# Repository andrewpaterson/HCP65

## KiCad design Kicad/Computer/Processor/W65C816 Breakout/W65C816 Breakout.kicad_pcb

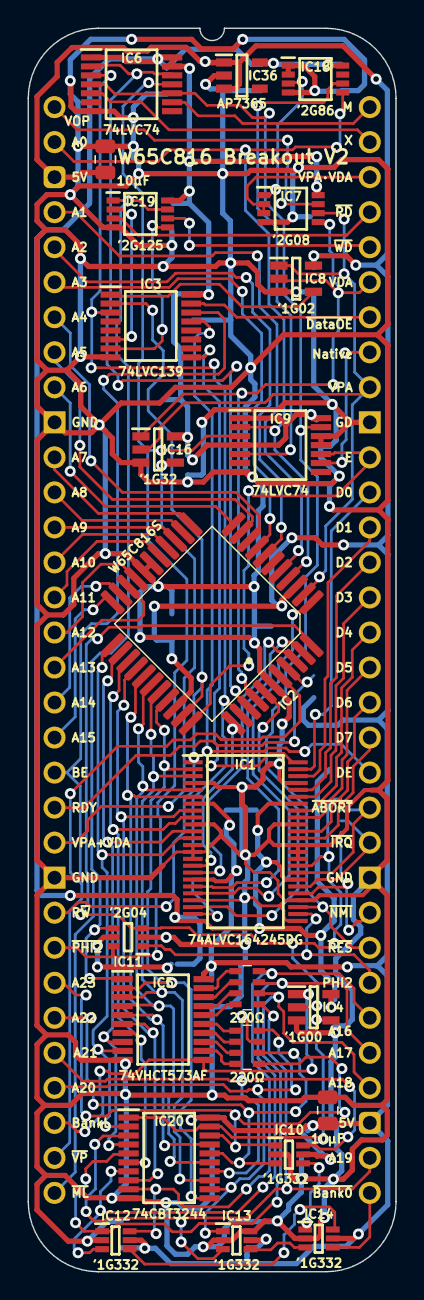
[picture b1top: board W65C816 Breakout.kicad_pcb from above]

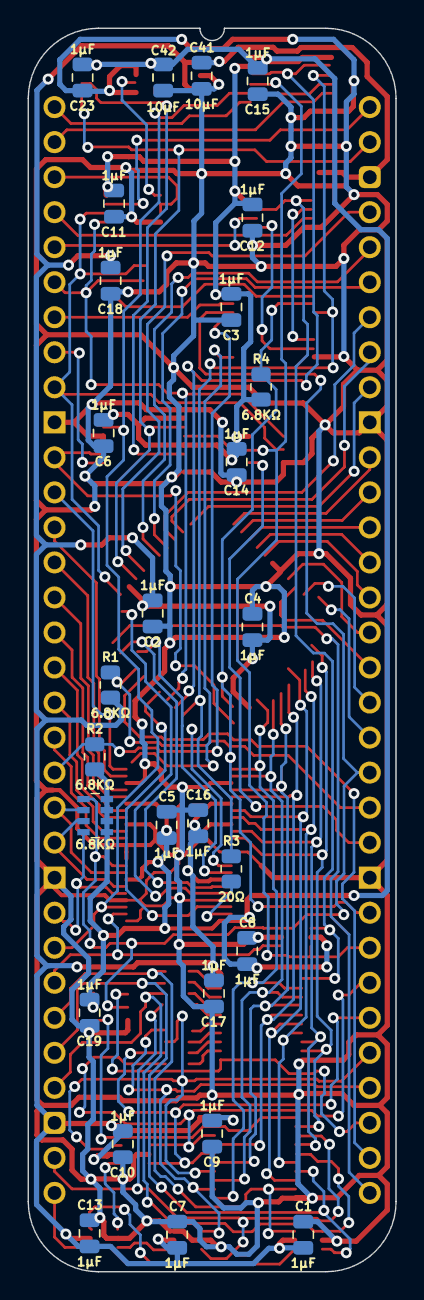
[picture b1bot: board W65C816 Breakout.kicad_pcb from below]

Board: 2 copper layers, 26.7 x 90.2 mm, 51 parts (27 on the bottom side), 96 nets.

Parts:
C1, C2, C3, C4, C5, C6, C7, C8, C9, C10, C11, C12, C13, C14, C15, C16, C17, C18, C19, C23: 1μF; C_0805
C20, C21, C41, C42: 10μF; C_0805
IC1: 74ALVC164245DGG,11; SOP50P810X120-48N
IC2: W65C816S6TQG-14; W65C816 PLCC 0.8mm 44 Pin
IC3: 74LVC139PW,118; SOP65P640X110-16N
IC4: 74LVC1G00GV,125; SOT95P275X110-5N
IC5: 74VHCT573AFT; SOP65P640X120-20N
IC6, IC9: 74LVC74APW,118; SOP65P640X110-14N
IC7: 74LVC2G08DP-Q100H; SOP65P400X110-8N
IC8: 74LVC1G02GV,125; SOT95P275X110-5N
IC10, IC12, IC13, IC14: SN74LVC1G332DCKRG4; SOT65P210X110-6N
IC11: 74LVC2G04GW-Q100H; SOP65P210X110-6N
IC16: 74LVC1G32GV,125; SOT95P275X110-5N
IC18: 74LVC2G86DP,125; SOP65P400X110-8N
IC19: 74LVC2G125DP,125; SOP65P400X110-8N
IC20: SN74CBT3244CPWR; SOP65P640X120-20N
IC36: AP7365-33WG-7; SOT95P285X130-5N
J7: Board 2x32 W22.86mm; DIP-64_Board_W22.86mm
R1, R2, R4: 6.8KΩ; R_0805
R3: 20Ω; R_0805
RN1, RN2: CAY16-221J4LF; CAY16-F4
RN4: CAY16-472J4LF; CAY16-F4

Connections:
5V: C1.1, C2.1, C4.1, C7.1, C9.1, C10.1, C13.1, C16.1, C17.1, C18.1, C20.1, C21.1, C41.1, IC1.7 (5V), IC1.18 (5V), IC2.9 (VCC), IC2.37 (VCC), IC5.20 (5V), IC8.5 (3V), IC10.5 (3V), IC12.5 (3V), IC13.5 (3V), IC14.5 (3V), IC20.20 (5V), IC36.1 (6VIn), IC36.3 (EN), J7.3, J7.35, R1.1
/3.3V: C3.1, C5.1, C6.1, C8.1, C11.1, C12.1, C14.1, C15.1, C19.1, C23.1, C42.1, IC1.24 (2DIR), IC1.31 (3V), IC1.42 (3V), IC3.16 (3V), IC4.5 (3V), IC6.1 (~1RD), IC6.13 (~2RD), IC6.14 (3V), IC7.8 (3V), IC9.1 (~1RD), IC9.4 (~1SD), IC9.14 (3V), IC11.5 (3V), IC16.5 (3V), IC18.8 (VCC), IC19.8 (VCC), IC36.5 (3.3VOut), R2.1, R4.1, RN4.1 (R1), RN4.2 (R2), RN4.3 (R3), RN4.4 (R4)
/A0_{CHANGE}: IC7.1 (1A), IC18.3 (2Y)
/A0_{PREV}: IC9.5 (1Q), IC18.6 (2B)
/BA0+BA1+BA2: IC12.4 (Y), IC14.6 (C)
/BA3+BA4: IC13.4 (Y), IC14.3 (B)
/BA5+BA6+BA7: IC10.4 (Y), IC14.1 (A)
/BE_{5V}: IC1.16 (2B2), IC2.40 (BE)
/D0_{65}: IC1.2 (1B0), IC2.36 (D0), IC5.2 (D0), IC20.11 (2A1)
/D0_{VHC}: IC5.19 (Q0), RN2.1 (R1)
/D1_{65}: IC1.3 (1B1), IC2.35 (D1), IC5.3 (D1), IC20.13 (2A2)
/D1_{VHC}: IC5.18 (Q1), RN2.2 (R2)
/D2_{65}: IC1.5 (1B2), IC2.34 (D2), IC5.4 (D2), IC20.15 (2A3)
/D2_{VHC}: IC5.17 (Q2), RN2.3 (R3)
/D3_{65}: IC1.6 (1B3), IC2.33 (D3), IC5.5 (D3), IC20.17 (2A4)
/D3_{VHC}: IC5.16 (Q3), RN2.4 (R4)
/D4_{65}: IC1.8 (1B4), IC2.32 (D4), IC5.6 (D4), IC20.8 (1A4)
/D4_{VHC}: IC5.15 (Q4), RN1.1 (R1)
/D5_{65}: IC1.9 (1B5), IC2.31 (D5), IC5.7 (D5), IC20.6 (1A3)
/D5_{VHC}: IC5.14 (Q5), RN1.2 (R2)
/D6_{65}: IC1.11 (1B6), IC2.30 (D6), IC5.8 (D6), IC20.4 (1A2)
/D6_{VHC}: IC5.13 (Q6), RN1.3 (R3)
/D7_{65}: IC1.12 (1B7), IC2.29 (D7), IC5.9 (D7), IC20.2 (1A1)
/D7_{VHC}: IC5.12 (Q7), RN1.4 (R4)
/FET ~OE: IC4.4 (Y), IC20.1 (1~OE), IC20.19 (2~OE)
/MX: IC2.42 (MX), IC6.2 (1D), IC6.12 (2D)
/PHI2_{5V}: IC2.41 (PHI2), IC3.3 (1A1), IC6.3 (1CP), R3.2
/~ABORT_{5V}: IC1.17 (2B3), IC2.4 (~ABORT)
/~BE: IC5.1 (~OE), IC11.4 (2Y), IC19.1 (1~OE), IC19.7 (2~OE)
/~DE: IC1.48 (1~OE), IC3.9 (~2Y3)
/~IRQ_{5V}: IC1.19 (2B4), IC2.5 (~IRQ)
/~NMI_{5V}: IC1.20 (2B5), IC2.7 (~NMI)
/~RD_{PART}: IC3.7 (~1Y3), IC19.5 (2A)
/~RES_{5V}: IC1.22 (2B6), IC2.44 (~RES)
/~VPA+VDA: IC3.1 (~1E), IC8.4 (Y)
/~WD_{PART}: IC3.6 (~1Y2), IC19.2 (1A)
A0: IC2.10 (A0), IC9.2 (1D), IC18.5 (2A), J7.2
A1: IC2.11 (A1), J7.4
A2: IC2.13 (A2), J7.5
A3: IC2.14 (A3), J7.6
A4: IC2.15 (A4), J7.7
A5: IC2.16 (A5), J7.8
A6: IC2.17 (A6), J7.9
A7: IC2.18 (A7), J7.11
A8: IC2.19 (A8), J7.12
A9: IC2.20 (A9), J7.13
A10: IC2.21 (A10), J7.14
A11: IC2.22 (A11), J7.15
A12: IC2.25 (A12), J7.16
A13: IC2.26 (A13), J7.17
A14: IC2.27 (A14), J7.18
A15: IC2.28 (A15), J7.19
Address Valid: IC16.4 (Y), J7.22
BA0: IC12.6 (C), IC20.9 (2B1), J7.38, RN2.8 (R1)
BA1: IC12.3 (B), IC20.7 (2B2), J7.37, RN2.7 (R2)
BA2: IC12.1 (A), IC20.5 (2B3), J7.36, RN2.6 (R3)
BA3: IC13.3 (B), IC20.3 (2B4), J7.34, RN2.5 (R4)
BA4: IC13.1 (A), IC20.12 (1B4), J7.29, RN1.8 (R1)
BA5: IC10.6 (C), IC20.14 (1B3), J7.28, RN1.7 (R2)
BA6: IC10.3 (B), IC20.16 (1B2), J7.27, RN1.6 (R3)
BA7: IC10.1 (A), IC20.18 (1B1), J7.26, RN1.5 (R4)
BE: IC1.33 (2A2), IC3.14 (2A0), IC4.2 (A), IC11.3 (2A), J7.20, RN4.5 (R4)
Bank Latch: IC4.1 (B), IC5.11 (LE), J7.30
D0: IC1.47 (1A0), J7.53
D1: IC1.46 (1A1), J7.52
D2: IC1.44 (1A2), J7.51
D3: IC1.43 (1A3), J7.50
D4: IC1.41 (1A4), J7.49
D5: IC1.40 (1A5), J7.48
D6: IC1.38 (1A6), J7.47
D7: IC1.37 (1A7), J7.46
DE: IC3.13 (2A1), J7.45, R2.2
E: IC2.39 (E), IC9.10 (~2SD), J7.54
GND: C1.2, C2.2, C3.2, C4.2, C5.2, C6.2, C7.2, C8.2, C9.2, C10.2, C11.2, C12.2, C13.2, C14.2, C15.2, C16.2, C17.2, C18.2, C19.2, C20.2, C21.2, C23.2, C41.2, C42.2, IC1.4 (GND), IC1.10 (GND), IC1.13 (2B0), IC1.14 (2B1), IC1.15 (GND), IC1.21 (GND), IC1.25 (2~OE), IC1.28 (GND), IC1.34 (GND), IC1.35 (2A1), IC1.36 (2A0), IC1.39 (GND), IC1.45 (GND), IC2.1 (GND), IC2.23 (GND), IC2.24 (GND), IC3.8 (GND), IC4.3 (GND), IC5.10 (GND), IC6.7 (GND), IC7.4 (GND), IC8.3 (GND), IC9.7 (GND), IC9.11 (2CP), IC9.12 (2D), IC10.2 (GND), IC11.2 (GND), IC12.2 (GND), IC13.2 (GND), IC13.6 (C), IC14.2 (GND), IC16.3 (GND), IC18.1 (1A), IC18.2 (1B), IC18.4 (GND), IC19.4 (GND), IC20.10 (GND), IC36.2 (GND), J7.10, J7.23, J7.42, J7.55
M: IC6.9 (2Q), J7.64
Native Latch: IC9.9 (2Q), J7.57
unnamed: IC1.23 (2B7), R3.1
Opcode Valid: IC7.7 (1Y), J7.1
PHI2: IC1.26 (2A7), IC11.1 (1A), J7.39
RDY: IC2.3 (RDY), J7.21, R1.2
R~W: IC1.1 (1DIR), IC2.38 (R~W), IC3.2 (1A0), J7.24, R4.2
VDA: IC2.43 (VDA), IC7.5 (2A), IC8.2 (A), IC16.1 (B), J7.59
VPA: IC2.8 (VPA), IC7.6 (2B), IC8.1 (B), IC16.2 (A), J7.56
VPA·VDA: IC7.2 (1B), IC7.3 (2Y), J7.62
X: IC6.5 (1Q), J7.63
~ABORT: IC1.32 (2A3), J7.44, RN4.6 (R3)
~BANK 0: IC14.4 (Y), J7.33
~Data Output: IC3.15 (~2E), J7.58
~IRQ: IC1.30 (2A4), J7.43, RN4.7 (R2)
~ML: IC2.6 (~ML), J7.32
~NMI: IC1.29 (2A5), J7.41, RN4.8 (R1)
~PHI2: IC6.11 (2CP), IC9.3 (1CP), IC11.6 (1Y), J7.25
~RD: IC19.3 (2Y), J7.61
~Reset: IC1.27 (2A6), IC6.4 (~1SD), IC6.10 (~2SD), IC9.13 (~2RD), J7.40
~VP: IC2.2 (~VP), J7.31
~WD: IC19.6 (1Y), J7.60

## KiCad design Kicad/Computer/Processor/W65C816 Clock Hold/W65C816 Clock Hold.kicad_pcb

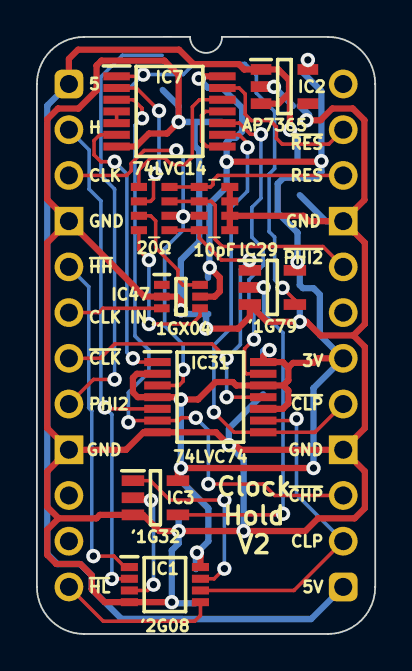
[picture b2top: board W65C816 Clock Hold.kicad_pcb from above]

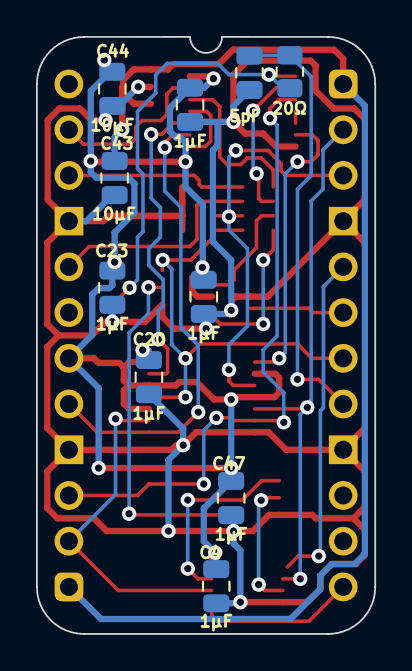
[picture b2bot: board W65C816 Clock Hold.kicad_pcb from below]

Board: 2 copper layers, 18.8 x 33.2 mm, 20 parts (10 on the bottom side), 28 nets.

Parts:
C1: 5pF; C_0805
C4, C20, C21, C23, C47, C56: 1μF; C_0805
C43, C44: 10μF; C_0805
CN1: CA0612KRX7R9BB100
IC1: 74LVC2G08DP-Q100H; SOP65P400X110-8N
IC2: AP7365-33WG-7; SOT95P285X130-5N
IC3: 74LVC1G32GV,125; SOT95P275X110-5N
IC7: SN74LVC14APWRG4; SOP65P640X110-14N
IC29: 74LVC1G79GV,125; SOT95P275X110-5N
IC31: 74LVC74APW,118; SOP65P640X110-14N
IC47: 74LVC1GX04GW,125; SOP65P210X110-6N
J1: Board 2x12 W22.86mm; DIP-24_Board_W15.24mm
R1: 20Ω; R_0805
RN1: CAY16-200J4LF; CAY16-F4

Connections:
3.3V: C4.1, C20.1, C21.1, C23.1, C44.1, C47.1, C56.1, IC1.8 (3V), IC2.5 (3.3VOut), IC3.5 (3V), IC7.14 (3V), IC29.5 (3V), IC31.2 (1D), IC31.4 (~1SD), IC31.10 (~2SD), IC31.12 (2D), IC31.14 (3V), IC47.5 (3V), J1.18
5V: C43.1, IC2.1 (6VIn), IC2.3 (EN), J1.1, J1.13
/CLK H.P.: IC7.4 (2Y), IC7.5 (3A)
/CLK L.P.: IC7.8 (4Y), IC7.11 (5A)
/High Pulse+Low Pulse: IC3.4 (Y), IC29.2 (CP)
/PHI2 Sharp: IC7.1 (1A), IC29.4 (Q), R1.2
/~CLK High Reset Pulse: IC7.6 (3Y), IC31.1 (~1RD)
/~CLK Low Reset Pulse: IC7.10 (5Y), IC31.13 (~2RD)
/~Hold High·CLK High Pulse·L=C: IC1.7 (1Y), IC3.1 (B)
/~Hold Low·CLK Low Pulse: IC1.3 (2Y), IC3.2 (A)
CLK: CN1.3, IC31.3 (1CP), J1.3, RN1.6 (R3)
CLK High Pulse: IC1.2 (1B), IC31.5 (1Q), J1.2
CLK IN: IC47.3 (X1), J1.6
CLK Low Pulse: IC1.6 (2B), IC31.9 (2Q), J1.14
GND: C1.2, C4.2, C20.2, C21.2, C23.2, C43.2, C44.2, C47.2, C56.2, CN1.5, CN1.6, CN1.7, CN1.8, IC1.4 (GND), IC2.2 (GND), IC3.3 (GND), IC7.7 (GND), IC29.3 (GND), IC31.7 (GND), IC47.2 (GND), J1.4, J1.9, J1.16, J1.21
unnamed: IC7.2 (1Y), RN1.2 (R2)
unnamed: IC7.12 (6Y), RN1.1 (R1)
unnamed: IC47.6 (Y), RN1.3 (R3)
unnamed: IC47.4 (~Y), RN1.4 (R4)
PHI2: C1.1, J1.8, R1.1
Reset: CN1.1, J1.22, RN1.8 (R1)
~CLK High Pulse: IC7.3 (2A), IC31.6 (~1Q), J1.15
~CLK Low Pulse: IC7.9 (4A), IC31.8 (~2Q), J1.17
~CLK: CN1.4, IC29.1 (D), IC31.11 (2CP), J1.7, RN1.5 (R4)
~Hold High: IC1.1 (1A), J1.5
~Hold Low: IC1.5 (2A), J1.12
~PHI2: CN1.2, J1.20, RN1.7 (R2)
~Reset: IC7.13 (6A), J1.23

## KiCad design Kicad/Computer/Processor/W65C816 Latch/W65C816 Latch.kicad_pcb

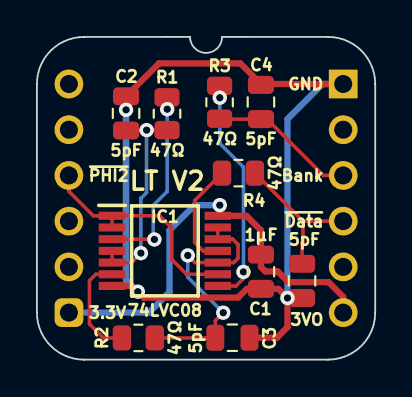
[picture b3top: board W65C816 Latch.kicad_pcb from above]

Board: 2 copper layers, 18.8 x 17.9 mm, 11 parts (0 on the bottom side), 11 nets.

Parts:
C1: 1μF; C_0805
C2, C3, C4, C5: 5pF; C_0805
IC1: 74LVC08APW,112; SOP65P640X110-14N
J2: Board 2x06 W15.24mm; DIP-12_Board_W15.24mm_Alt
R1, R2, R3, R4: 47Ω; R_0805

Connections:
3.3V: C1.1, IC1.14 (3V), J2.6, J2.7
/~PHI2_{2}: C2.1, IC1.4 (2A), IC1.5 (2B), R1.1
/~PHI2_{3}: C3.1, IC1.10 (3B), IC1.12 (4A), IC1.13 (4B), R2.1
Bank Latch: C4.1, J2.10, R3.1
GND: C1.2, C2.2, C3.2, C4.2, C5.2, IC1.7 (GND), J2.12
unnamed: IC1.3 (1Y), R1.2
unnamed: IC1.6 (2Y), R2.2
unnamed: IC1.8 (3Y), R3.2
unnamed: IC1.11 (4Y), R4.2
~Data Output: C5.1, J2.9, R4.1
~PHI2: IC1.1 (1A), IC1.2 (1B), IC1.9 (3A), J2.3

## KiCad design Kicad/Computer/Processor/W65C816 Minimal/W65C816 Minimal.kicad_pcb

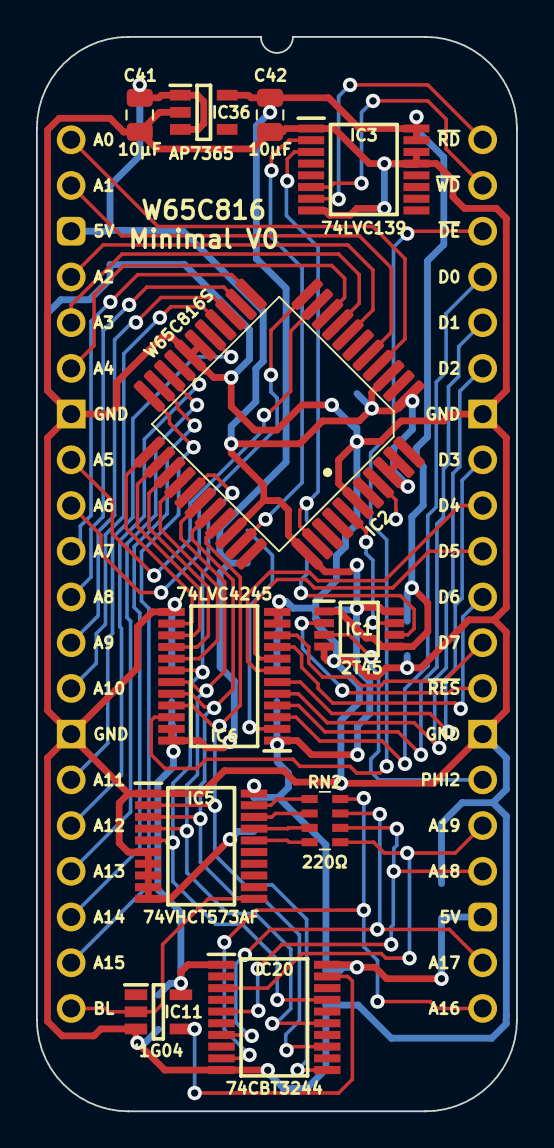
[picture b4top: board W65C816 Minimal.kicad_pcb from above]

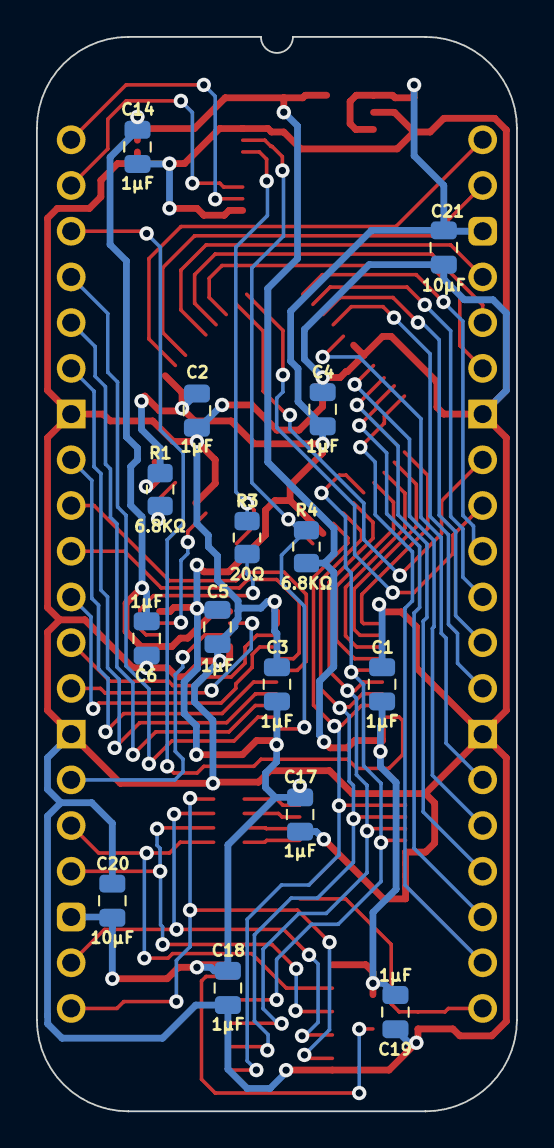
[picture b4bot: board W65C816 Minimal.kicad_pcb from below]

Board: 2 copper layers, 26.7 x 59.7 mm, 27 parts (15 on the bottom side), 55 nets.

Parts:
C1, C2, C3, C4, C5, C6, C14, C17, C18, C19: 1μF; C_0805
C20, C21, C41, C42: 10μF; C_0805
IC1: SN74LVC2T45DCTR; SOP65P400X130-8N
IC2: W65C816S6TQG-14; W65C816 PLCC 0.8mm 44 Pin
IC3: 74LVC139PW,118; SOP65P640X110-16N
IC5: 74VHCT573AFT; SOP65P640X120-20N
IC6: 74LVC4245APW,118; SOP65P640X110-24N
IC11: 74LVC1G04GV,125; SOT95P275X110-5N
IC20: SN74CBT3244CPWR; SOP65P640X120-20N
IC36: AP7365-33WG-7; SOT95P285X130-5N
J3: Board 2x20 W22.86mm; DIP-40_Board_W22.86mm
R1, R4: 6.8KΩ; R_0805
R3: 20Ω; R_0805
RN2: CAY16-221J4LF; CAY16-F4

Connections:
5V: C2.1, C3.1, C4.1, C5.1, C17.1, C18.1, C20.1, C21.1, C41.1, IC1.8 (5V), IC2.4 (~ABORT), IC2.5 (~IRQ), IC2.7 (~NMI), IC2.9 (VCC), IC2.37 (VCC), IC2.40 (BE), IC5.20 (5V), IC6.1 (5V), IC20.20 (5V), IC36.1 (6VIn), IC36.3 (EN), J3.3, J3.23, R1.2
/3.3V: C1.1, C6.1, C14.1, C19.1, C42.1, IC1.1 (3V), IC1.5 (DIR), IC3.15 (~2E), IC3.16 (3V), IC6.23 (3V), IC6.24 (3V), IC11.5 (3V), IC20.1 (1~OE), IC36.5 (3.3VOut), R4.1
/D0_{65}: IC2.36 (D0), IC5.2 (D0), IC6.21 (B0), IC20.11 (2A1)
/D0_{VHC}: IC5.19 (Q0), RN2.1 (R1)
/D1_{65}: IC2.35 (D1), IC5.3 (D1), IC6.20 (B1), IC20.13 (2A2)
/D1_{VHC}: IC5.18 (Q1), RN2.2 (R2)
/D2_{65}: IC2.34 (D2), IC5.4 (D2), IC6.19 (B2), IC20.15 (2A3)
/D2_{VHC}: IC5.17 (Q2), RN2.3 (R3)
/D3_{65}: IC2.33 (D3), IC5.5 (D3), IC6.18 (B3), IC20.17 (2A4)
/D3_{VHC}: IC5.16 (Q3), RN2.4 (R4)
/D4_{65}: IC2.32 (D4), IC6.17 (B4)
/D5_{65}: IC2.31 (D5), IC6.16 (B5)
/D6_{65}: IC2.30 (D6), IC6.15 (B6)
/D7_{65}: IC2.29 (D7), IC6.14 (B7)
/PHI2_{5V}: IC2.41 (PHI2), IC3.3 (1A1), R3.2
/PHI2_{5V}T: IC1.6 (B1), R3.1
/R~W: IC2.38 (R~W), IC3.2 (1A0), IC6.2 (DIR), R4.2
/~RES_{5V}: IC1.7 (B0), IC2.44 (~RES)
A0: IC2.10 (A0), J3.1
A1: IC2.11 (A1), J3.2
A2: IC2.13 (A2), J3.4
A3: IC2.14 (A3), J3.5
A4: IC2.15 (A4), J3.6
A5: IC2.16 (A5), J3.8
A6: IC2.17 (A6), J3.9
A7: IC2.18 (A7), J3.10
A8: IC2.19 (A8), J3.11
A9: IC2.20 (A9), J3.12
A10: IC2.21 (A10), J3.13
A11: IC2.22 (A11), J3.15
A12: IC2.25 (A12), J3.16
A13: IC2.26 (A13), J3.17
A14: IC2.27 (A14), J3.18
A15: IC2.28 (A15), J3.19
BA0: IC20.9 (2B1), J3.21, RN2.8 (R1)
BA1: IC20.7 (2B2), J3.22, RN2.7 (R2)
BA2: IC20.5 (2B3), J3.24, RN2.6 (R3)
BA3: IC20.3 (2B4), J3.25, RN2.5 (R4)
Bank Latch: IC5.11 (LE), IC11.2 (A), J3.20
D0: IC6.3 (A0), J3.37
D1: IC6.4 (A1), J3.36
D2: IC6.5 (A2), J3.35
D3: IC6.6 (A3), J3.33
D4: IC6.7 (A4), J3.32
D5: IC6.8 (A5), J3.31
D6: IC6.9 (A6), J3.30
D7: IC6.10 (A7), J3.29
GND: C1.2, C2.2, C3.2, C4.2, C5.2, C6.2, C14.2, C17.2, C18.2, C19.2, C20.2, C21.2, C41.2, C42.2, IC1.4 (GND), IC2.1 (GND), IC2.23 (GND), IC2.24 (GND), IC3.1 (~1E), IC3.8 (GND), IC3.13 (2A1), IC3.14 (2A0), IC5.1 (~OE), IC5.6 (D4), IC5.7 (D5), IC5.8 (D6), IC5.9 (D7), IC5.10 (GND), IC6.11 (GND), IC6.12 (GND), IC6.13 (GND), IC11.3 (GND), IC20.10 (GND), IC36.2 (GND), J3.7, J3.14, J3.27, J3.34
unnamed: IC2.3 (RDY), R1.1
unnamed: IC11.4 (Y), IC20.19 (2~OE)
PHI2: IC1.3 (A1), J3.26
~DE: IC6.22 (~OE), J3.38
~RD: IC3.7 (~1Y3), J3.40
~Reset: IC1.2 (A0), J3.28
~WD: IC3.6 (~1Y2), J3.39

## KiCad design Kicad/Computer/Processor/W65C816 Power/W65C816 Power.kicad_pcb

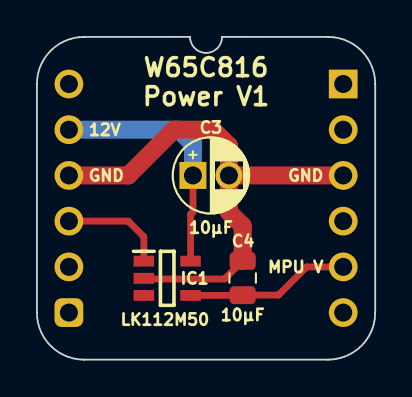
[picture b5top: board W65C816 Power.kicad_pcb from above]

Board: 2 copper layers, 18.8 x 17.9 mm, 4 parts (0 on the bottom side), 4 nets.

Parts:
C3: 10μF; CP_Radial_D4.0mm_P2.00mm
C4: 10µF; C_0805
IC1: LK112M50TR; SOT95P285X130-5N
J2: Board 2x06 W15.24mm; DIP-12_Board_W15.24mm_Alt

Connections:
5V: IC1.1 (~SHDN), J2.4
12V: C3.1, IC1.5 (14VIn), J2.2
GND: C3.2, C4.2, IC1.2 (GND), J2.3, J2.10
W65C816V: C4.1, IC1.4 (5.0VOut), J2.8

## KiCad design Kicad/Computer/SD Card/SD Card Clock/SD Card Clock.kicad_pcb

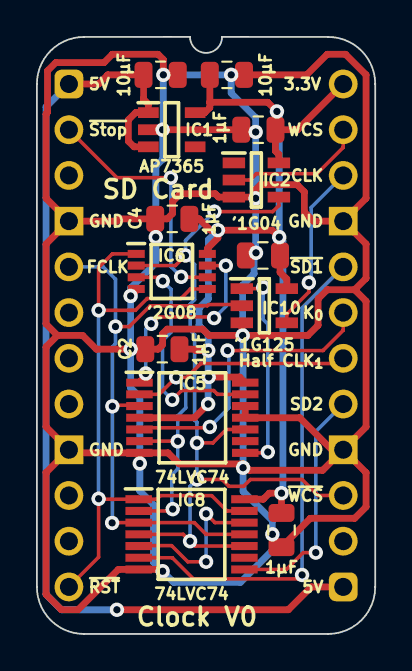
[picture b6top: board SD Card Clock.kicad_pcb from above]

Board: 2 copper layers, 18.8 x 33.2 mm, 14 parts (0 on the bottom side), 17 nets.

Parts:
C1, C2, C4, C5, C7: 1μF; C_0805
C10, C11: 10µF; C_0805
IC1: AP7365-33WG-7; SOT95P285X130-5N
IC2: 74LVC1G04GV,125; SOT95P275X110-5N
IC5, IC8: 74LVC74APW,118; SOP65P640X110-14N
IC6: 74LVC2G08DP-Q100H; SOP65P400X110-8N
IC10: 74LVC1G125GV-Q100; SOT95P275X110-5N
J2: Board 2x12 W15.24mm; DIP-24_Board_W15.24mm

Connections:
3.3V: C1.1, C2.1, C4.1, C5.1, C7.1, C11.1, IC1.5 (3.3VOut), IC2.5 (3V), IC5.4 (~1SD), IC5.14 (3V), IC6.8 (3V), IC8.14 (3V), IC10.5 (3V), J2.24
5V: C10.1, IC1.1 (6VIn), IC1.3 (EN), J2.1, J2.13
/CLK ~OE: IC5.8 (~2Q), IC10.1 (~OE)
/Second Half CLK_{Dragged1}: IC8.5 (1Q), IC8.12 (2D)
/~Reset Clock Flop: IC5.1 (~1RD), IC6.7 (1Y)
/~Reset Transmit: IC5.13 (~2RD), IC6.3 (2Y)
Fast CLK: IC5.3 (1CP), IC8.3 (1CP), IC8.11 (2CP), IC10.2 (A), J2.5
First Half CLK: IC5.5 (1Q), J2.19
GND: C1.2, C2.2, C4.2, C5.2, C7.2, C10.2, C11.2, IC1.2 (GND), IC2.3 (GND), IC5.7 (GND), IC5.11 (2CP), IC5.12 (2D), IC6.4 (GND), IC8.7 (GND), IC10.3 (GND), J2.4, J2.9, J2.16, J2.21
SD CLK: IC10.4 (Y), J2.22
Second Half CLK: IC5.2 (1D), IC5.6 (~1Q), IC8.2 (1D), J2.18
Write Read Start: IC2.2 (A), J2.23
~Reset: IC6.1 (1A), IC6.5 (2A), IC8.1 (~1RD), IC8.13 (~2RD), J2.12
~Second Half CLK_{Dragged1}: IC8.6 (~1Q), J2.20
~Second Half CLK_{Dragged2}: IC8.8 (~2Q), J2.17
~Stop Funk: IC6.6 (2B), J2.2
~Write Read Start: IC2.4 (Y), IC5.10 (~2SD), IC6.2 (1B), IC8.4 (~1SD), IC8.10 (~2SD), J2.15

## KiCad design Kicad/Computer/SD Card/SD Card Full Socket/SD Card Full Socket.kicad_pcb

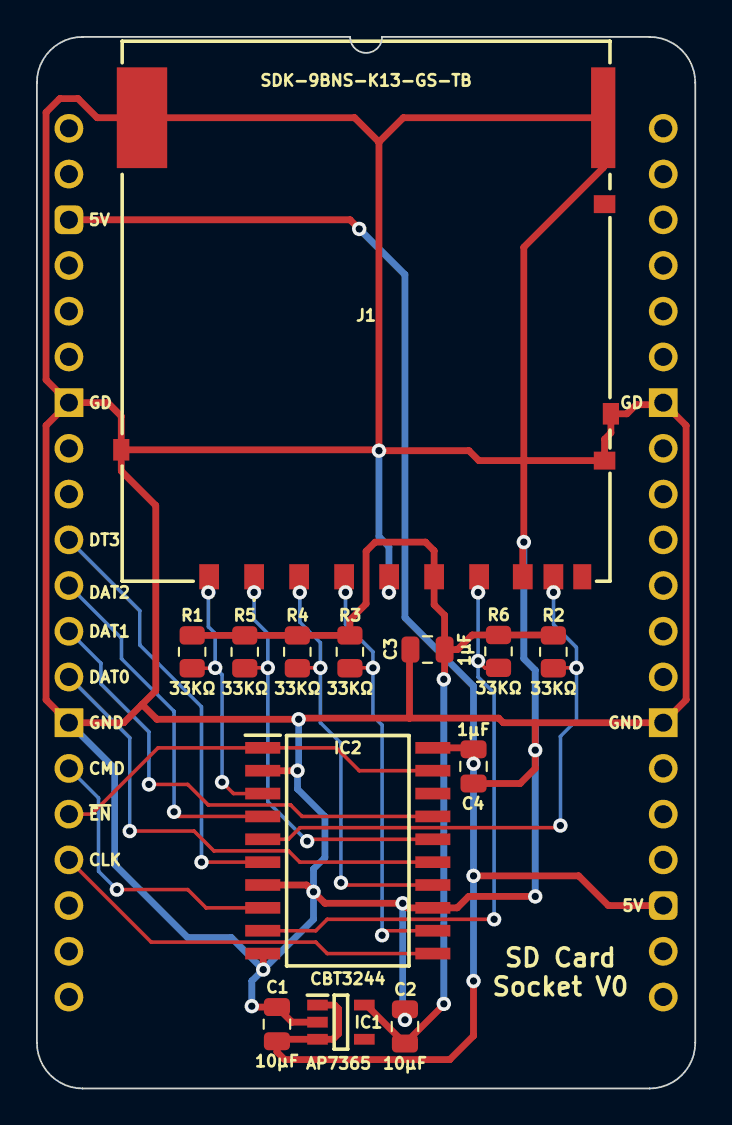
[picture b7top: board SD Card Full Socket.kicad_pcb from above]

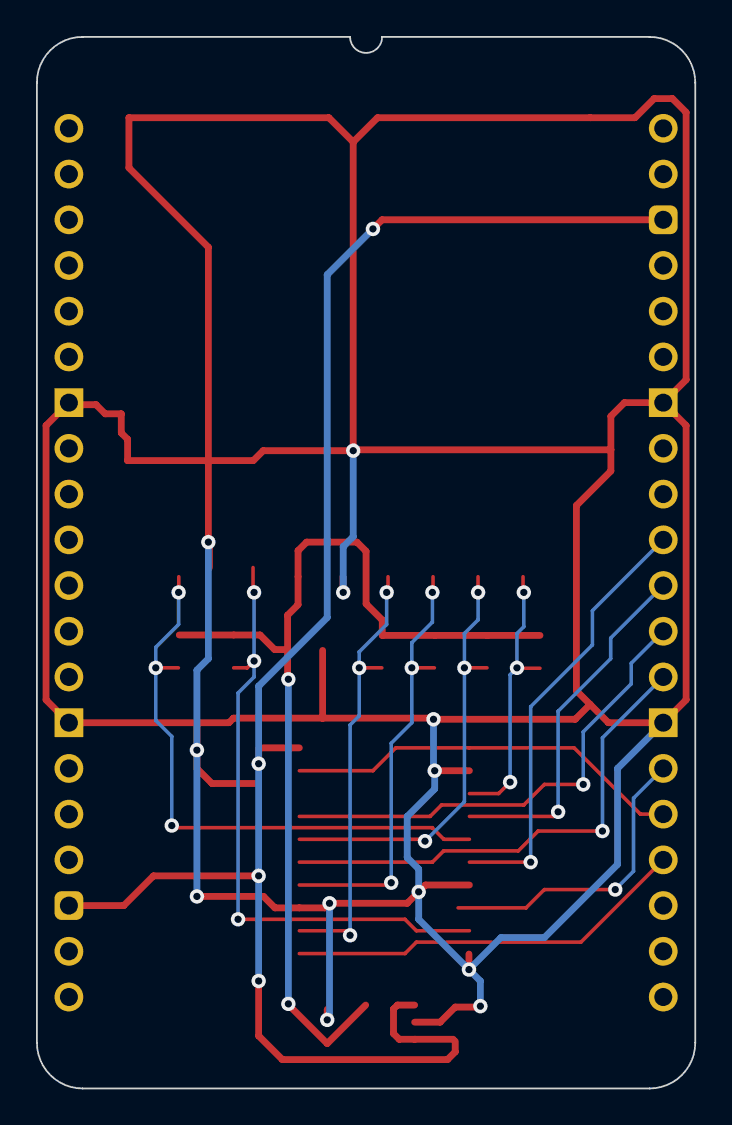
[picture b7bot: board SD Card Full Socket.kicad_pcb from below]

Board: 2 copper layers, 36.6 x 58.4 mm, 17 parts (2 on the bottom side), 16 nets.

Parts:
C1, C2: 10μF; C_0805
C3, C4: 1μF; C_0805
IC1: AP7365-33WG-7; SOT95P285X130-5N
IC2: CBT3244AD,112; SOIC127P1032X265-20N
J1: SDK-9BNS-K13-GS-TB_LF__SN_1; SDK9BNSK13GSTBLFSN1
J2, J3: Pin_Header_01x20; PinHeader_1x20_P2.54mm_Vertical
J5, J6: Conn_01x20; SIP_20_Pins
R1, R2, R3, R4, R5, R6: 33KΩ; R_0805

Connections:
5V: C1.1, C4.1, IC1.1 (6VIn), IC1.3 (EN), IC2.20 (5V), J5.3, J6.3
/3.3V: C2.1, C3.1, IC1.5 (3.3VOut), J1.5 (VDD), R1.2, R2.2, R3.2, R4.2, R5.2, R6.2
DAT0: IC2.15 (2A3), J5.13
DAT1: IC2.17 (2A4), J5.12
DAT2: IC2.4 (1A2), J5.11
DAT3: IC2.6 (1A3), J5.10
GND: C1.2, C2.2, C3.2, C4.2, IC1.2 (GND), IC2.2 (1A1), IC2.7 (2B2), IC2.10 (GND), IC2.13 (2A2), J1.4 (VSS), J1.7 (VSS), J1.G1 (TERMINAL_GND), J1.G2 (SHELL_GND_1), J1.G3 (SHELL_GND_2), J1.G4 (SHELL_GND_3), J1.G5 (SHELL_GND_4), J5.7, J5.14, J6.7, J6.14
unnamed: IC2.16 (1B2), J1.1 (DAT2), R5.1
unnamed: IC2.14 (1B3), J1.2 (CD/DAT3), R4.1
unnamed: IC2.12 (1B4), J1.3 (CMD), R3.1
unnamed: IC2.9 (2B1), J1.6 (CLK), R6.1
unnamed: IC2.5 (2B3), J1.8 (DAT0), R2.1
unnamed: IC2.3 (2B4), J1.9 (DAT1), R1.1
SD CLK: IC2.11 (2A1), J5.17
SD CMD: IC2.8 (1A4), J5.15
~SD Card Enable: IC2.1 (1~OE), IC2.19 (2~OE), J5.16

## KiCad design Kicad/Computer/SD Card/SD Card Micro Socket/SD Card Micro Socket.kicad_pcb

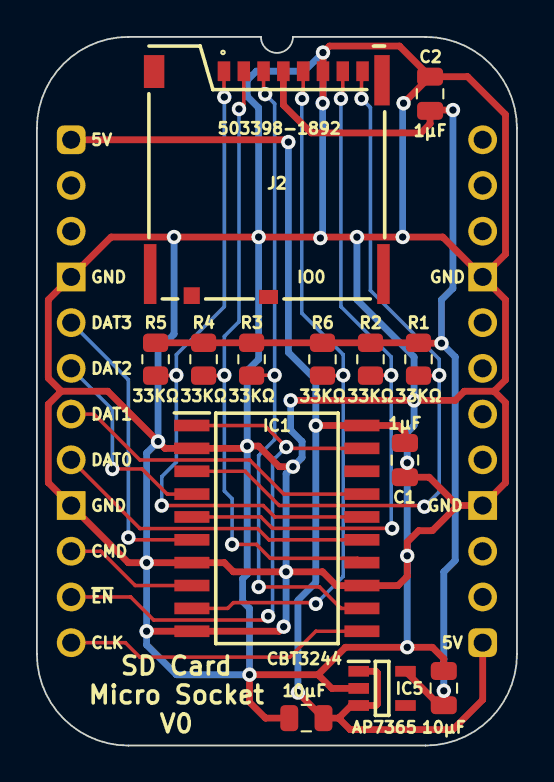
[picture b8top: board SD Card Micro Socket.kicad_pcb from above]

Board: 2 copper layers, 26.7 x 39.4 mm, 14 parts (0 on the bottom side), 16 nets.

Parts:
C1, C2: 1μF; C_0805
C3, C4: 10µF; C_0805
IC1: CBT3244AD,112; SOIC127P1032X265-20N
IC5: AP7365-33WG-7; SOT95P285X130-5N
J1: Board 2x12 W22.86mm; DIP-24_Board_W22.86mm
J2: 503398-1892
R1, R2, R3, R4, R5, R6: 33KΩ; R_0805

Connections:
5V: C1.1, C3.1, IC1.20 (5V), IC5.1 (6VIn), IC5.3 (EN), J1.1, J1.13
/3.3V: C2.1, C4.1, IC5.5 (3.3VOut), J2.4 (VDD), R1.2, R2.2, R3.2, R4.2, R5.2, R6.2
DAT0: IC1.15 (2A3), J1.8
DAT1: IC1.17 (2A4), J1.7
DAT2: IC1.4 (1A2), J1.6
DAT3: IC1.6 (1A3), J1.5
GND: C1.2, C2.2, C3.2, C4.2, IC1.2 (1A1), IC1.7 (2B2), IC1.10 (GND), IC1.13 (2A2), IC5.2 (GND), J1.4, J1.9, J1.16, J1.21, J2.6 (VSS)
unnamed: IC1.16 (1B2), J2.1 (DAT2), R5.1
unnamed: IC1.14 (1B3), J2.2 (CD/DAT3), R4.1
unnamed: IC1.12 (1B4), J2.3 (CMD), R3.1
unnamed: IC1.9 (2B1), J2.5 (CLK), R6.1
unnamed: IC1.5 (2B3), J2.7 (DAT0), R2.1
unnamed: IC1.3 (2B4), J2.8 (DAT1), R1.1
SD CLK: IC1.11 (2A1), J1.12
SD CMD: IC1.8 (1A4), J1.10
~SD Card Enable: IC1.1 (1~OE), IC1.19 (2~OE), J1.11
